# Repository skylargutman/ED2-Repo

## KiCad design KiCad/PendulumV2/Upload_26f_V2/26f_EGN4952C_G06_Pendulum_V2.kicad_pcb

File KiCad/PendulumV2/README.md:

# Pendulum Control Board V2: single ESP32

Board for the single-ESP32 rig (`cart/cart_single` v11.2). Replaces the V1 two-ESP32
board in `../Pendulum`. Saved in KiCad 9 format, which KiCad 10 opens and upgrades.

## What's on it

| Ref | Part | Connects to |
|---|---|---|
| U1 | NodeMCU-32S socket | pinout = header of `cart/cart_single/cart_single.ino` |
| U2 | 4-ch level shifter module | encoders 5 V → 3.3 V, LVn↔HVn straight through |
| J1 | 5 V screw terminal | off-board HW-536 buck (24 V never on this board) |
| J2 | 1x6 header | Pi by jumper wires, in the order of the R1-R7 stack: 1 TXD (Pi pin 8), 2 RXD (10), 3 START (36), 4 STOP (38), 5 READY (33), 6 GND. Never jumper Pi pin 2 or 4 (5 V) |
| J3 | 2x5 IDC | Feedback encoder cable (same pinout as V1 J10 / 10pinBoxAdapter) |
| J4/J5 | 1x5 | pendulum / cart encoder test points |
| J6 | 1x8 | 1 START, 3 STOP (NC), 5 LIMIT-L, 7 LIMIT-R, even pins GND |
| J7 | 1x8 | IBT-2 in its own pin order: RPWM LPWM R_EN L_EN R_IS L_IS VCC GND |

Pi lines have 330 Ω series resistors. START/STOP/READY have 10k pull-downs (keep R6 on
strapping pin GPIO5). Switch inputs have a 10k pull-up, 1k series and 100n filter. RPWM/LPWM have
10k pull-downs so the motor stays off while the ESP32 boots.

## Changes from V1 to check

- **Level shifter:** V1 crossed the channels (LV1/LV2 to cart pins, HV1/HV2 to pendulum lines).
  V2 is straight through. If the encoders come out swapped, swap the cables or the labels.
  Don't re-cross the board.
- **Encoder pull-ups and filter caps removed (2026-11-09):** R9–R12 (4.7k) and C6–C9 (1 nF) are gone; the breadboard
  runs without them and the level-shifter module has its own pull-ups. If counts go missing with the motor running,
  add 1 nF from each encoder line to GND (not 100 nF: V1's 4.7k × 100n = 0.47 ms lost edges).
- **IBT-2 enables:** R_EN/L_EN are tied to +5 V.
- **Pi power pins:** the Pi's 3V3/5V pins are not connected. The board shares GND only.
- **USB and 5 V:** the ESP32 is powered from the 5 V terminal. Before you leave USB plugged in
  with the 5 V terminal live, check the DevKit has a diode on VBUS.

## Status

- ERC: clean (only "library not in config" warnings from an unconfigured kicad-cli).
- Schematic ↔ PCB parity: clean. The netlist was checked net by net against the design.
- PCB: routed with Freerouting 2.4.1 on 2026-10-27: 0 unconnected items, 0 clearance
  violations. Net classes: Power (GND, +5V, +3V3) 1.0 mm, Default 0.4 mm, 0.508 mm
  clearance (V1's board minimum). Ground is carried by the F.Cu/B.Cu pours only; the
  autorouted GND traces were removed, and DRC confirms every GND pad still connects.
  Same 147.5 × 120.5 mm outline and M3 hole positions as V1.
- Known DRC warnings: 26 silkscreen overlaps (cosmetic). 2 starved thermals: R22 pad 2
  touches a small F.Cu pour island, and J5 pin 1 has one spoke. Both are connected through
  the B.Cu pour.
- `Gerber/` and `*_gerbers.zip` are from **before** the GND traces were removed. Re-export
  before ordering.
- The custom footprints in `Skylar.pretty` were recovered from the V1 board, because the original
  `Skylar.pretty` folder isn't in the repo.

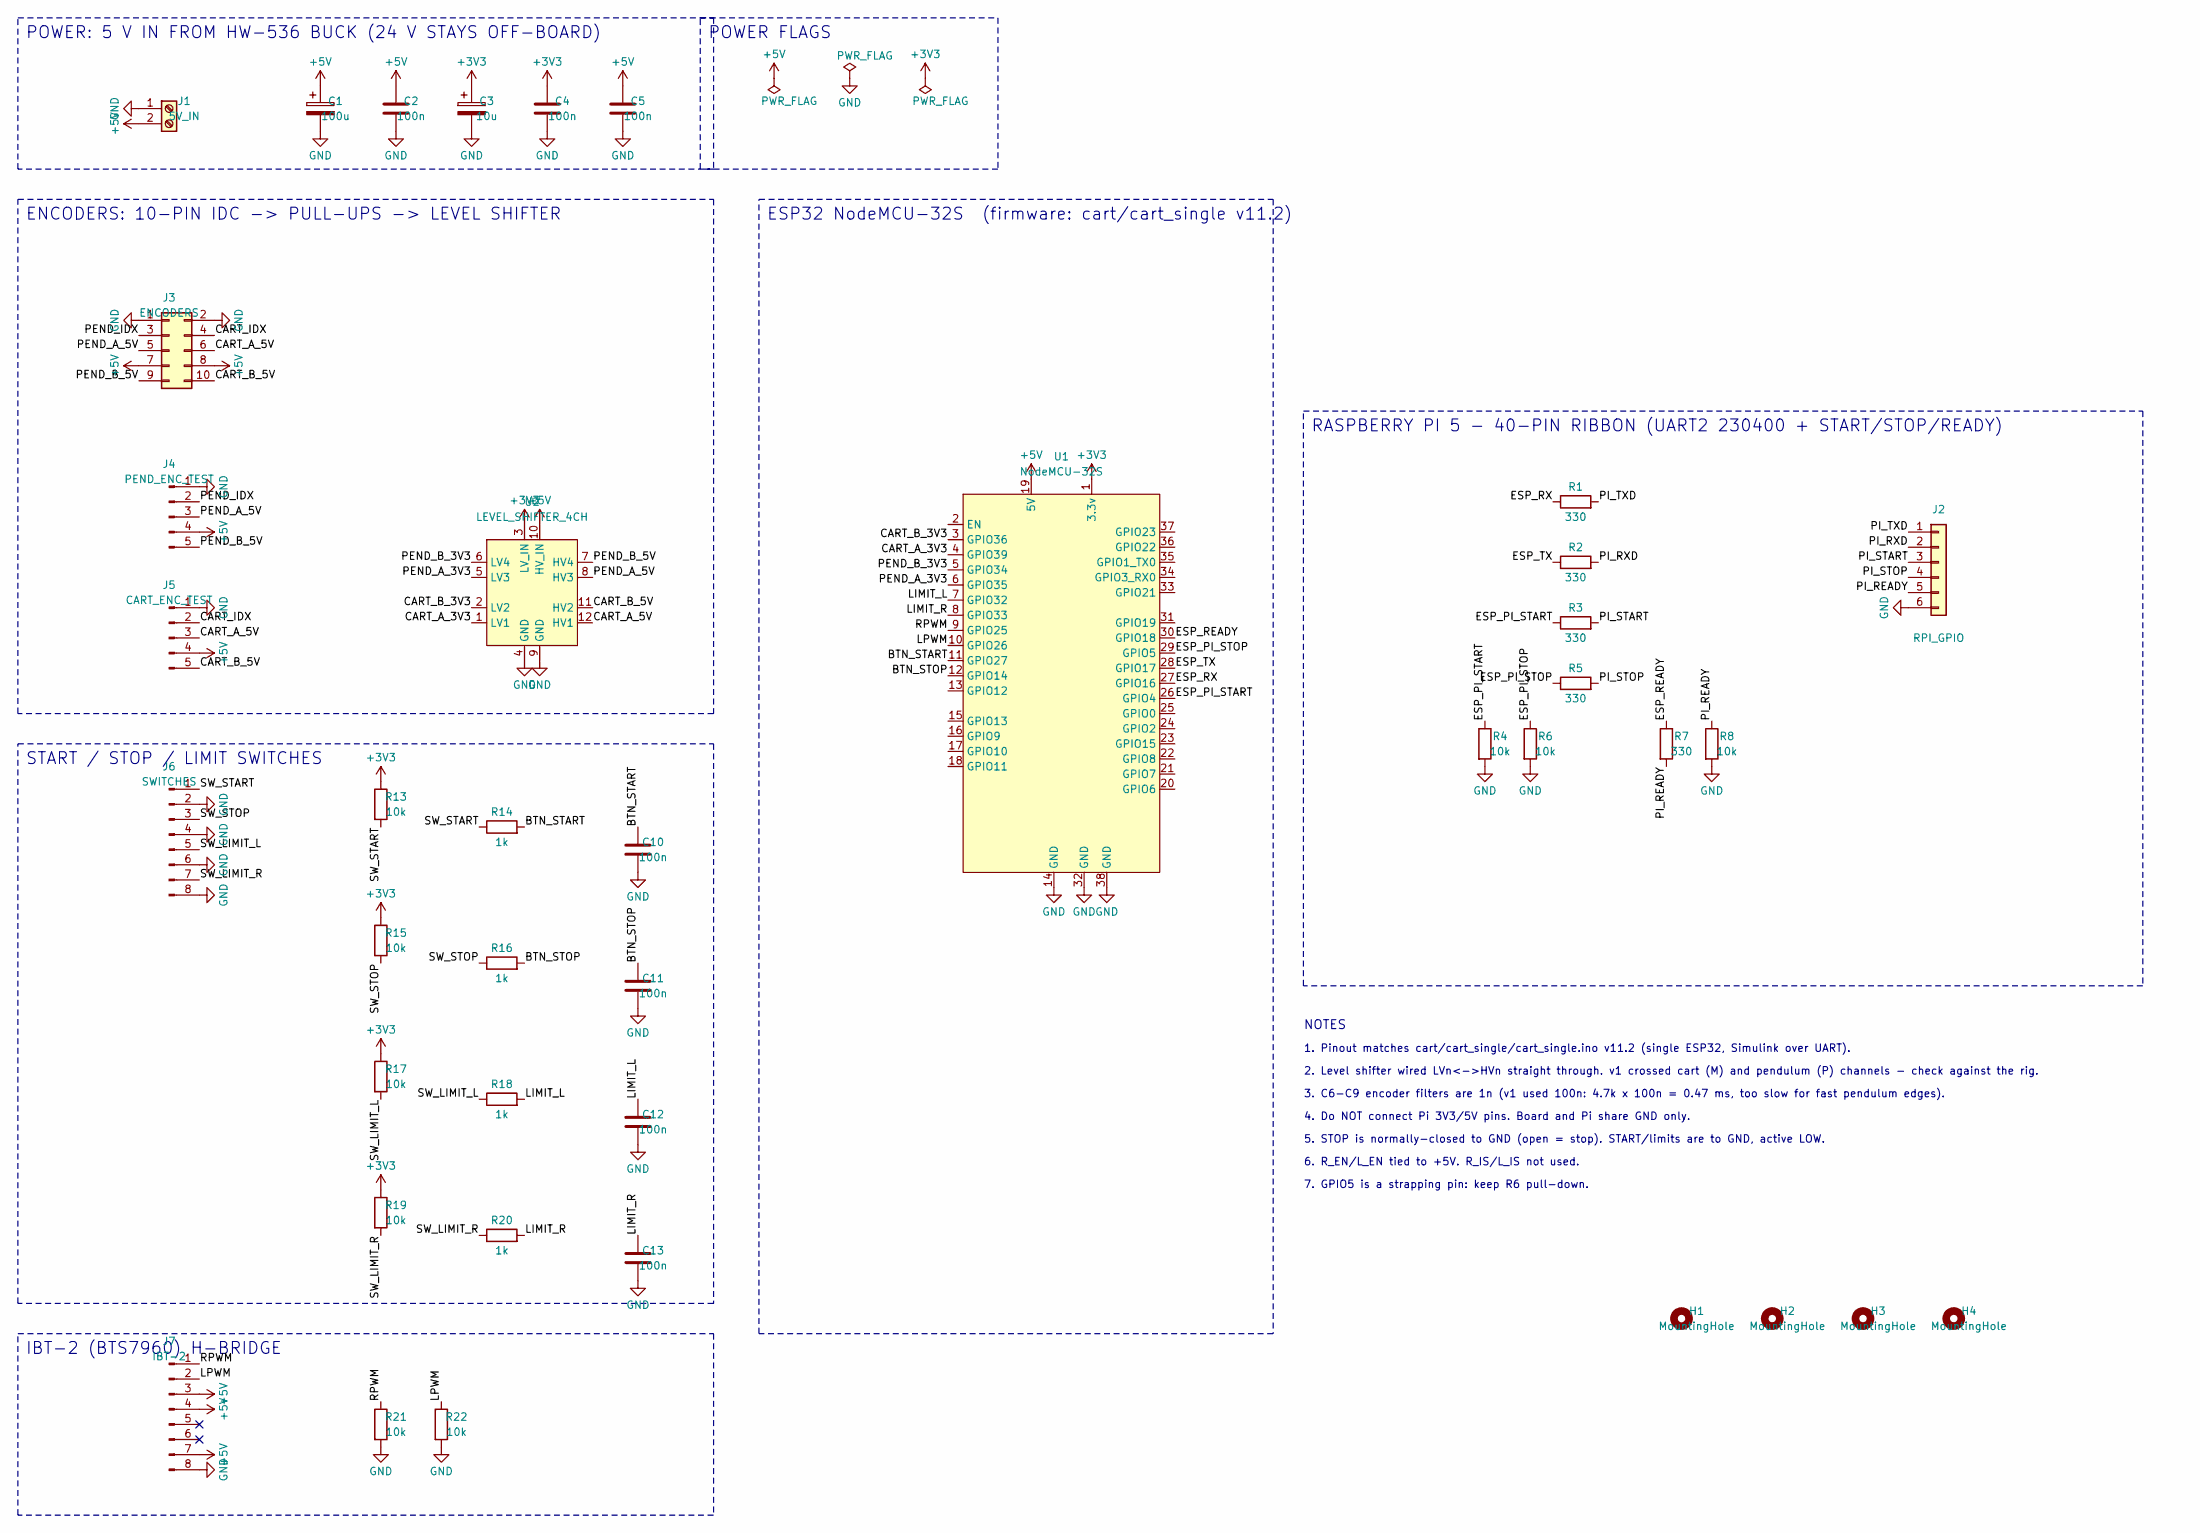
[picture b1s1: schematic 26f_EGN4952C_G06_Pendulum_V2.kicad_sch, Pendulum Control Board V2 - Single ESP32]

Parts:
C1: 100u; CP_Radial_D8.0mm_P3.50mm
C2, C4, C5, C10, C11, C12, C13: 100n; C_Disc_D5.0mm_W2.5mm_P5.00mm
C3: 10u; CP_Radial_D5.0mm_P2.50mm
H1, H2, H3, H4: MountingHole; MountingHole_3.2mm_M3
J1: 5V_IN; TerminalBlock_Phoenix_MKDS-3-2-5.08_1x02_P5.08mm_Horizontal
J2: RPI_GPIO; PinHeader_1x06_P2.54mm_Vertical
J3: ENCODERS; IDC-Header_2x05_P2.54mm_Vertical
J4: PEND_ENC_TEST; PinHeader_1x05_P2.54mm_Vertical
J5: CART_ENC_TEST; PinHeader_1x05_P2.54mm_Vertical
J6: SWITCHES; PinHeader_1x08_P2.54mm_Vertical
J7: IBT-2; PinHeader_1x08_P2.54mm_Vertical
R1, R2, R3, R5, R7: 330; R_Axial_DIN0207_L6.3mm_D2.5mm_P7.62mm_Horizontal
R4, R6, R8, R13, R15, R17, R19, R21, R22: 10k; R_Axial_DIN0207_L6.3mm_D2.5mm_P7.62mm_Horizontal
R14, R16, R18, R20: 1k; R_Axial_DIN0207_L6.3mm_D2.5mm_P7.62mm_Horizontal
U1: NodeMCU-32S; ESP32_38pin_DoubleRow
U2: LEVEL_SHIFTER_4CH; LEVEL_SHIFT

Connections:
+3V3: C3.1, C4.1, R13.1, R15.1, R17.1, R19.1, U1.1 (3.3v), U2.3 (LV_IN)
+5V: C1.1, C2.1, C5.1, J1.2, J3.7, J3.8, J4.4, J5.4, J7.3, J7.4, J7.7, U1.19 (5V), U2.10 (HV_IN)
/BTN_START: C10.1, R14.2, U1.11 (GPIO27)
/BTN_STOP: C11.1, R16.2, U1.12 (GPIO14)
/CART_A_3V3: U1.4 (GPIO39), U2.1 (LV1)
/CART_A_5V: J3.6, J5.3, U2.12 (HV1)
/CART_B_3V3: U1.3 (GPIO36), U2.2 (LV2)
/CART_B_5V: J3.10, J5.5, U2.11 (HV2)
/CART_IDX: J3.4, J5.2
/ESP_PI_START: R3.1, R4.1, U1.26 (GPIO4)
/ESP_PI_STOP: R5.1, R6.1, U1.29 (GPIO5)
/ESP_READY: R7.1, U1.30 (GPIO18)
/ESP_RX: R1.1, U1.27 (GPIO16)
/ESP_TX: R2.1, U1.28 (GPIO17)
/LIMIT_L: C12.1, R18.2, U1.7 (GPIO32)
/LIMIT_R: C13.1, R20.2, U1.8 (GPIO33)
/LPWM: J7.2, R22.1, U1.10 (GPIO26)
/PEND_A_3V3: U1.6 (GPIO35), U2.5 (LV3)
/PEND_A_5V: J3.5, J4.3, U2.8 (HV3)
/PEND_B_3V3: U1.5 (GPIO34), U2.6 (LV4)
/PEND_B_5V: J3.9, J4.5, U2.7 (HV4)
/PEND_IDX: J3.3, J4.2
/PI_READY: J2.5, R7.2, R8.1
/PI_RXD: J2.2, R2.2
/PI_START: J2.3, R3.2
/PI_STOP: J2.4, R5.2
/PI_TXD: J2.1, R1.2
/RPWM: J7.1, R21.1, U1.9 (GPIO25)
/SW_LIMIT_L: J6.5, R17.2, R18.1
/SW_LIMIT_R: J6.7, R19.2, R20.1
/SW_START: J6.1, R13.2, R14.1
/SW_STOP: J6.3, R15.2, R16.1
GND: C1.2, C2.2, C3.2, C4.2, C5.2, C10.2, C11.2, C12.2, C13.2, J1.1, J2.6, J3.1, J3.2, J4.1, J5.1, J6.2, J6.4, J6.6, J6.8, J7.8, R4.2, R6.2, R8.2, R21.2, R22.2, U1.14 (GND), U1.32 (GND), U1.38 (GND), U2.4 (GND), U2.9 (GND)

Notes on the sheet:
ENCODERS: 10-PIN IDC -> PULL-UPS -> LEVEL SHIFTER
5. STOP is normally-closed to GND (open = stop). START/limits are to GND, active LOW.
6. R_EN/L_EN tied to +5V. R_IS/L_IS not used.
2. Level shifter wired LVn<->HVn straight through. v1 crossed cart (M) and pendulum (P) channels - check against the rig.
3. C6-C9 encoder filters are 1n (v1 used 100n: 4.7k x 100n = 0.47 ms, too slow for fast pendulum edges).
POWER FLAGS
IBT-2 (BTS7960) H-BRIDGE
START / STOP / LIMIT SWITCHES
NOTES
1. Pinout matches cart/cart_single/cart_single.ino v11.2 (single ESP32, Simulink over UART).
7. GPIO5 is a strapping pin: keep R6 pull-down.
POWER: 5 V IN FROM HW-536 BUCK (24 V STAYS OFF-BOARD)
ESP32 NodeMCU-32S (firmware: cart/cart_single v11.2)
RASPBERRY PI 5 - 40-PIN RIBBON (UART2 230400 + START/STOP/READY)
4. Do NOT connect Pi 3V3/5V pins. Board and Pi share GND only.

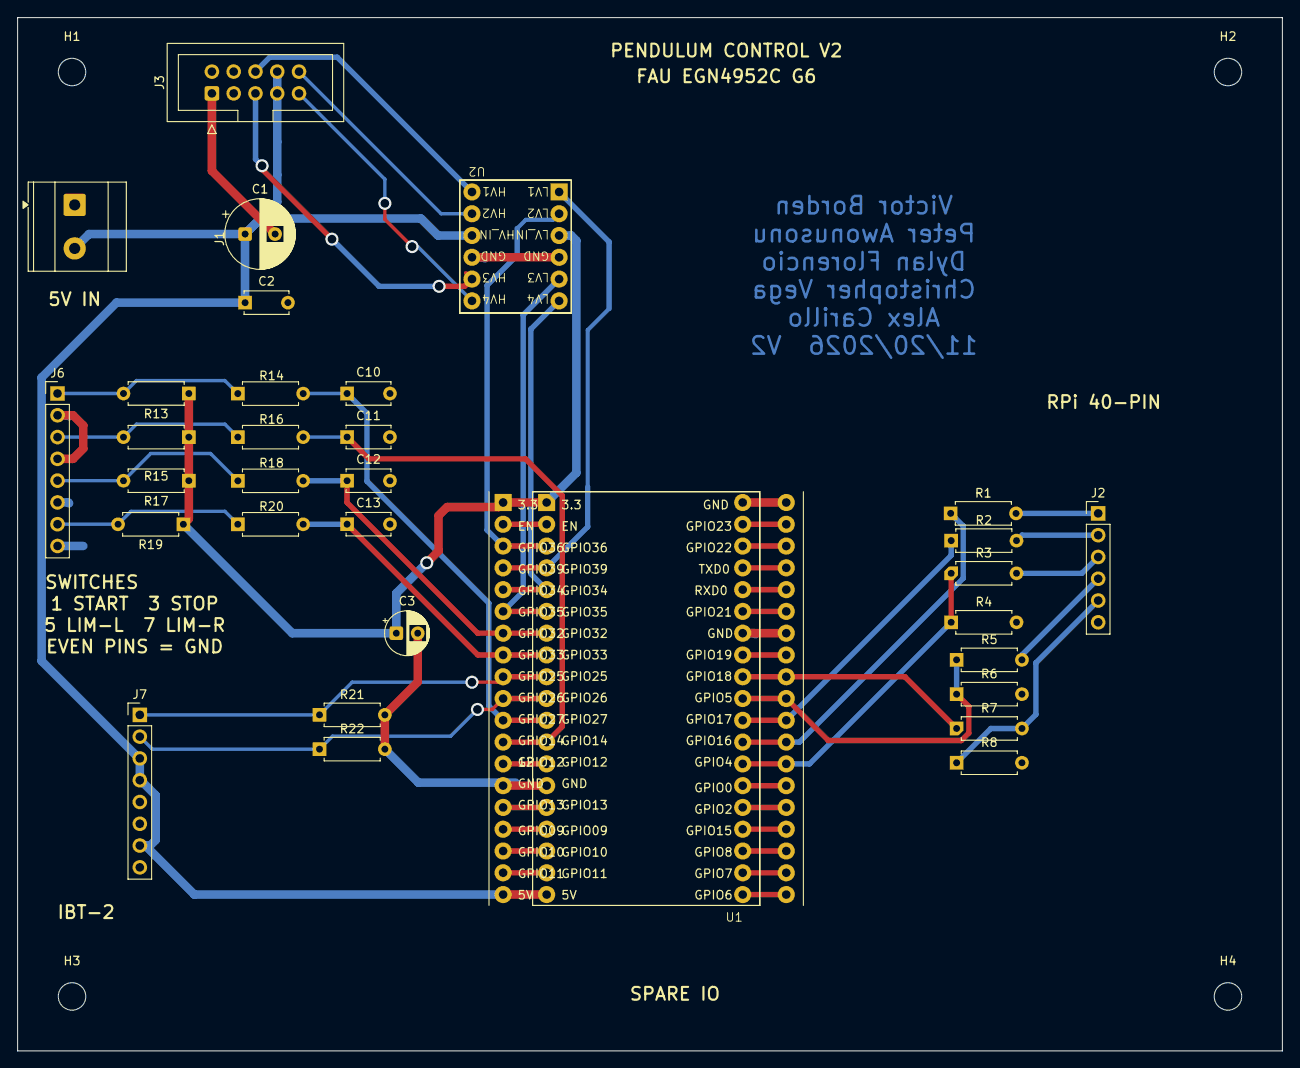
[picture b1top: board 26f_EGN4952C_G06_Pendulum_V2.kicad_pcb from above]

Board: 2 copper layers, 147.5 x 120.5 mm, 36 parts (0 on the bottom side), 31 nets.

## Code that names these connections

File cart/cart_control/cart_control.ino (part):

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//   - Boot banner printed first thing so the running version is obvious.
//
// Pin Assignments:
//   GPIO 25 : RPWM  (IBT-2)
//   GPIO 26 : LPWM  (IBT-2)
//   GPIO 27 : START button         (INPUT_PULLUP, active LOW)
//   GPIO 14 : STOP button          (INPUT_PULLUP, active LOW)
//   GPIO 32 : Left limit switch    (INPUT_PULLUP, active LOW)
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Adafruit_ADS1115 ads;

// --- Motor pins ---
#define RPWM_PIN      25
#define LPWM_PIN      26

// --- Button pins ---
#define START_BTN     27
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#define UART_RX       16

// --- Pi GPIO trigger pins ---
#define PI_START_PIN   4   // Pi GPIO 16, Pi Pin 36 — MQTT homing trigger
#define PI_STOP_PIN    5   // Pi GPIO 20, Pi Pin 38 — MQTT stop trigger

// --- Homing complete signal to Pi ---
#define HOMING_DONE_PIN 18  // Pi GPIO 13, Pi Pin 33 — HIGH when homing complete
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// Motor helpers
// =============================================================================
void stopMotor() {
  ledcWrite(RPWM_PIN, 0);
  ledcWrite(LPWM_PIN, 0);
}

void driveLeft(int pwm) {
  ledcWrite(RPWM_PIN, 0);
  ledcWrite(LPWM_PIN, pwm);
}

void driveRight(int pwm) {
  ledcWrite(RPWM_PIN, pwm);
  ledcWrite(LPWM_PIN, 0);
}

void drive(Dir d, int pwm) {
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// Trigger helpers — unify button and Pi GPIO inputs
// =============================================================================
bool startTriggered() {
  return (digitalRead(START_BTN) == LOW) || (digitalRead(PI_START_PIN) == HIGH) || serialStart;
}

bool stopTriggered() {
  // STOP_BTN is normally closed wired to GND:
  //   resting = closed = LOW = not stopped
  //   pressed = open   = HIGH (pulled up) = stopped
  return (digitalRead(STOP_BTN) == HIGH) || (digitalRead(PI_STOP_PIN) == HIGH) || serialStop;
}

// =============================================================================
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void setup() {
  // --- Hold motor outputs LOW immediately — prevents runaway on boot ---
  // Do this before ledcAttach so pins are driven low, not floating
  pinMode(RPWM_PIN, OUTPUT);
  pinMode(LPWM_PIN, OUTPUT);
  digitalWrite(RPWM_PIN, LOW);
  digitalWrite(LPWM_PIN, LOW);

  Serial.begin(115200);
  Serial.println();
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  clearHomingDone();

  // Now attach LEDC PWM (25kHz, 8-bit, above audible range)
  ledcAttach(RPWM_PIN, 25000, 8);
  ledcAttach(LPWM_PIN, 25000, 8);
  stopMotor();   // redundant but explicit

  // --- GPIO setup ---
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  pinMode(STOP_BTN,     INPUT_PULLUP);
  pinMode(LEFT_LIMIT,   INPUT_PULLUP);
  pinMode(RIGHT_LIMIT,  INPUT_PULLUP);
  pinMode(PI_START_PIN, INPUT_PULLDOWN);  // Pi drives HIGH to trigger
  pinMode(PI_STOP_PIN,  INPUT_PULLDOWN);  // Pi drives HIGH to trigger

  // --- UART2 ---
  // 7-byte packets every 2ms = 3.5 KB/s. The default 256-byte buffer overflows
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    delay(10);
  }
  Serial.println(serialStart ? "START from serial" :
                 digitalRead(PI_START_PIN) == HIGH ? "START from Pi" : "START from button");
  delay(200);  // debounce

  runHoming();
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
